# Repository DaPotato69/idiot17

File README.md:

# idiot17
The original idiotic keyboard

possibly the dumbest thing i have ever created
<br><br>
made with ergogen
firmware in idiot12 repository (yes i removed an extra 5 keys)

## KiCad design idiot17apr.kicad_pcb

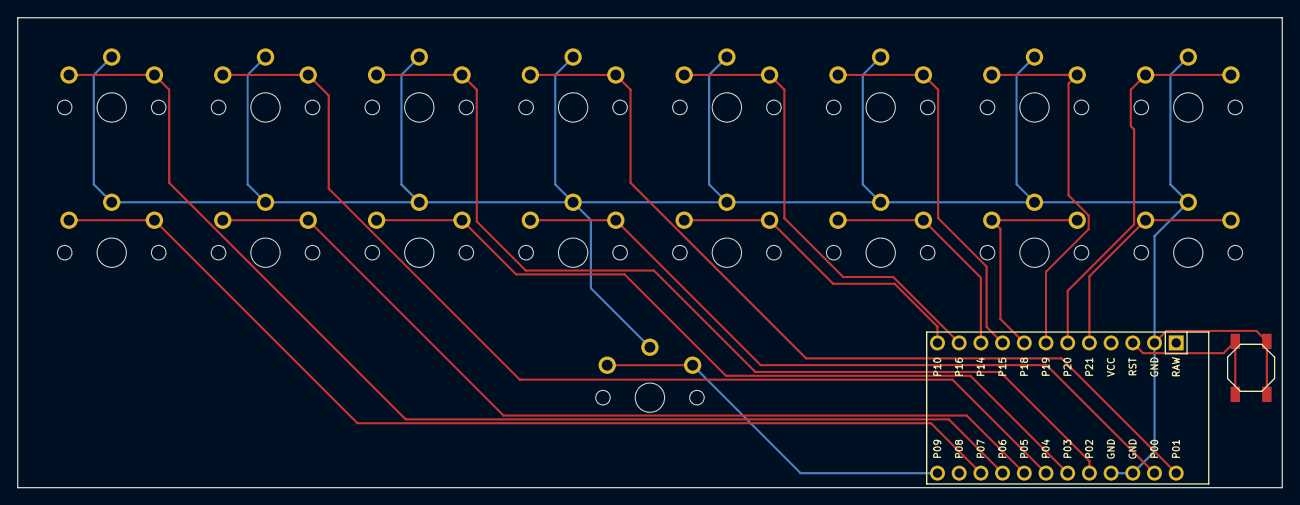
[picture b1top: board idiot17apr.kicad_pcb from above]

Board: 2 copper layers, 148.0 x 55.0 mm, 19 parts (0 on the bottom side), 19 nets.

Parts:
B1: SW_TACT_ALPS_SKQGABE010
MCU1: ProMicro
S1, S2, S3, S4, S5, S6, S7, S8, S9, S10, S11, S12, S13, S14, S15, S16, S17: PG1350

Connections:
GND: B1.1, MCU1.2, MCU1.15, MCU1.16, S1.2, S2.2, S3.2, S4.2, S5.2, S6.2, S7.2, S8.2, S9.2, S10.2, S11.2, S12.2, S13.2, S14.2, S15.2, S16.2, S17.2
P0: MCU1.14, S12.1
P1: MCU1.13, S4.1
P2: MCU1.17, S3.1
P3: MCU1.18, S11.1
P4: MCU1.19, S2.1
P5: MCU1.20, S10.1
P6: MCU1.21, S1.1
P7: MCU1.22, S9.1
P9: MCU1.24, S17.1
P10: MCU1.12, S13.1
P14: MCU1.10, S14.1
P15: MCU1.9, S6.1
P16: MCU1.11, S5.1
P18: MCU1.8, S15.1
P19: MCU1.7, S7.1
P20: MCU1.6, S8.1
P21: MCU1.5, S16.1
RST: B1.2, MCU1.3
